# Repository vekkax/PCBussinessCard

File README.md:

# PCB Business Card

The **PCB Business Card** is a hardware project inspired by the [Hackaday 2024 Business Card Contest](https://hackaday.io/contest/195949-2024-business-card-contest)   and the business cards created by [Salvaged Circuitry](https://www.youtube.com/watch?v=rEdWV4Augfc).

It is a compact and creative way to showcase your capabilities as a hardware designer while sharing your contact details. Beyond being a novelty, the card also functions as a (slightly impractical, but fun) development platform.

---

## Board Design

The PCB was designed using **KiCad**, along with plugins such as **KiKit** and the **Fabrication Toolkit** to generate production-ready files.

The board features:

- **[STM32L452CEU](Datasheets/stm32l452ce.pdf)** microcontroller  
- **[NT2H1311F0DTLH](Datasheets/NTAG213F_216F.pdf)** NFC tag  
- Integrated **PCB USB connector**  
- Optional **pin headers**, allowing the card to be used as a development board  

The USB connector supplies power to the microcontroller through a **[3.3 V LDO regulator](Datasheets/LM3480.pdf)** and includes ESD protection on the data lines using a **TVS diode**. A power LED is placed next to the connector for visual feedback.

The NFC tag is connected to a custom PCB antenna designed using NXP’s [NFC Antenna Design Tool](https://community.nxp.com/t5/NFC/bd-p/nfc).  
This tool provides a convenient interface to design PCB NFC antennas (especially for NXP tags/readers) based on user-defined constraints. ST also provides a similar [antenna design tool](https://eds.st.com/antenna/#/).

---

### Bill of Materials (BOM)

| Reference | Value | Footprint | Quantity |
|---------|------|-----------|----------|
| C1–C4, C7–C9 | 100 nF | 0402 | 7 |
| C5 | 10 nF | 0402 | 1 |
| C6 | 1 µF | 0402 | 1 |
| D1 | RCLAMP0582B | SOT-416 | 1 |
| D2 | LED | 0603 | 1 |
| IC1 | NT2H1311F0DTL | SOT1312AB2 | 1 |
| R1 | 120 Ω | 0603 | 1 |
| SW1 | SMD push button | 4.6×1.8×1.9 mm | 1 |
| U1 | STM32L452CEU | QFN-48 | 1 |
| U2 | LM3480-3.3 | SOT-23 | 1 |

> **Note**  
> Reference designators were removed from the PCB layout to improve the visual appearance of the board.

---

## Fabrication

For fabrication, **KiCad’s KiKit** and **JLCPCB’s Fabrication Toolkit** plugins were used.

### Panelization

KiKit was used to panelize the PCB. Each panel contains **four PCB business cards**, separated by mouse bites and surrounded by left and right rails.

The panel configuration file can be found here:  
`PCBussinesCard_Circuit/Panels/panel_config.json`

For more information on KiKit panelization, refer to the official documentation:  
https://yaqwsx.github.io/KiKit/latest/panelization/examples/

### Manufacturing

Manufacturing was done using **JLCPCB**, with production files generated via the JLCPCB Fabrication Toolkit plugin.

---

## Software

The USB connector is used to expose the board as a **USB Mass Storage Device**, allowing a host computer to read and write files (for example, a digital CV) directly to the microcontroller’s internal flash memory.

This implementation uses the STM32’s built-in **USB Full-Speed device** support and the **Mass Storage Class (MSC)**.

The implementation was based on and adapted from the following guide:  
[STM32 USB MSC using Flash Memory – Embetronicx](https://embetronicx.com/tutorials/microcontrollers/stm32/stm32-usb-device-msc-using-flash-memory/)

---

### Flash Memory Configuration

According to the [RM0394 Reference Manual](Datasheets/rm0394-stm32l41xxx42xxx43xxx44xxx45xxx46xxx-advanced-armbased-32bit-mcus-stmicroelectronics.pdf), the STM32L452 has **512 KB of flash memory** organized in a single bank.

In this project:
- **64 KB** of flash is reserved for USB mass storage
- Starting at **Page 127**
- Flash start address:  
  **`0x0803F800`**

---

## STM32CubeIDE Configuration

1. Create a new STM32CubeIDE project for the **STM32L452**.
2. Under **Connectivity**, enable **USB Device (FS)**.
3. In **Middleware and Software Packs → USB_DEVICE**:
   - Set the class to **Mass Storage Class**
   - Set `MSC_MEDIA_PACKET` to **32 KB (32768 bytes)**

4. Ensure the USB clock is configured at **48 MHz** in the clock configuration tab.

5. Generate the project code.

---

## USB Mass Storage Implementation

Open the file: ```usb_device/App/usbd_storage_if.c```

### Storage Parameters

```c
#define STORAGE_LUN_NBR    1
#define STORAGE_BLK_NBR    128      // 128 blocks × 512 bytes = 64 KB
#define STORAGE_BLK_SIZ    0x200    // 512 bytes
```
---
### Flash Write Function
A helper function is added to write data to flash memory:

```c
#include <stdbool.h>

#define USB_FLASH_START_ADDRESS   (  0x0803F800 )    //USB Flash Address (page 127 in STM32L452)
#define TOTAL_USB_DEVICE_SIZE   ( STORAGE_BLK_NBR * STORAGE_BLK_SIZ )

/**
  * @brief  Writes data into the FLASH.
  * @param  buf: data buffer.
  * @param  blk_addr: Logical block address.
  * @param  blk_len: Blocks number.
  * @retval HAL_StatusTypeDef
  */
static HAL_StatusTypeDef write_data_to_flash( uint8_t *buf, uint32_t blk_addr, uint16_t blk_len )
{
  HAL_StatusTypeDef ret = HAL_OK;
  uint8_t           data[ TOTAL_USB_DEVICE_SIZE ];

  do
  {
    /* First copy the data to the local buffer from Flash */
    memcpy( data, (const void *)USB_FLASH_START_ADDRESS, TOTAL_USB_DEVICE_SIZE );
    
    /* Make modifications in the local buffer */
    memcpy((void*)&data[blk_addr*STORAGE_BLK_SIZ], buf, (blk_len*STORAGE_BLK_SIZ));
    
    ret = HAL_FLASH_Unlock();
    if( ret != HAL_OK )
    {
      break;
    }
    
    /* Erase the Flash */
    FLASH_EraseInitTypeDef EraseInitStruct;
    uint32_t SectorError;
    EraseInitStruct.TypeErase     = FLASH_TYPEERASE_SECTORS;
    EraseInitStruct.Sector        = FLASH_SECTOR_6;
    EraseInitStruct.NbSectors     = 1;                    //erase 1 sector(6)
    EraseInitStruct.VoltageRange  = FLASH_VOLTAGE_RANGE_3;
    
    ret = HAL_FLASHEx_Erase( &EraseInitStruct, &SectorError );
    
    /* Write the data to the Flash */
    for( uint32_t i = 0; i < TOTAL_USB_DEVICE_SIZE; i++)
    {
      ret = HAL_FLASH_Program( FLASH_TYPEPROGRAM_BYTE,
                  ( USB_FLASH_START_ADDRESS + i ),
                  data[i]
                  );
    
      if( ret != HAL_OK )
      {
        break;
      }
    }
    
    HAL_FLASH_Lock();
  } while( false );

  return( ret );
}
```
The function:

1. Copies existing flash contents to a RAM buffer

2. Modifies the buffer with new data

3. Erases the corresponding flash sector

4. Writes the updated data back to flash

---
### Write Callback
```c
int8_t STORAGE_Write_FS(uint8_t lun, uint8_t *buf, uint32_t blk_addr, uint16_t blk_len)
{
  UNUSED(lun);
  return write_data_to_flash(buf, blk_addr, blk_len);
}

```
---
### Read Callback
Reading data is simpler and can be done directly from flash:

```c
int8_t STORAGE_Read_FS(uint8_t lun, uint8_t *buf, uint32_t blk_addr, uint16_t blk_len)
{
  UNUSED(lun);
  memcpy(
    buf,
    (const void *)(USB_FLASH_START_ADDRESS + (blk_addr * STORAGE_BLK_SIZ)),
    blk_len * STORAGE_BLK_SIZ
  );
  return USBD_OK;
}

```
---
### Usage
1. Flash the firmware to the board.

2. Connect the PCB Business Card via USB.

3. A removable USB drive will appear.

4. Format the drive if prompted.

5. Files can now be read from and written to the device.

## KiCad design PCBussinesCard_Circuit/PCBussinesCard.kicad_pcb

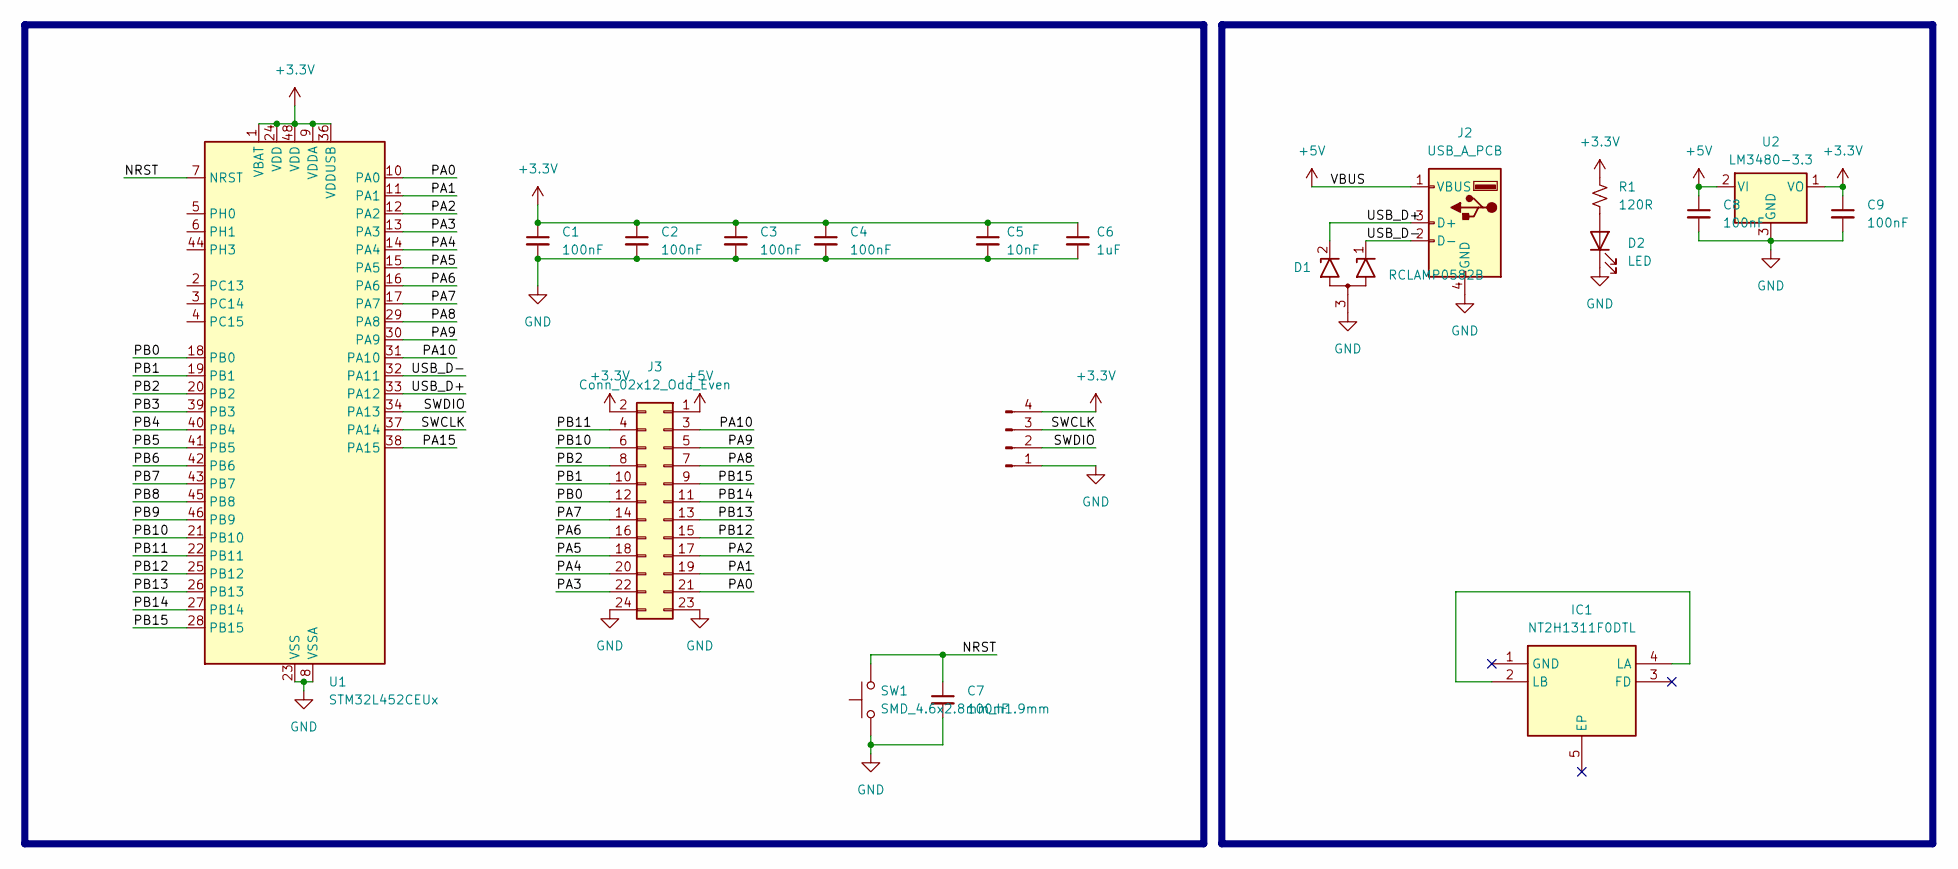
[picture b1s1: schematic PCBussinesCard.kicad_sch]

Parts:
C1, C2, C3, C4, C7, C8, C9: 100nF; C_0402_1005Metric
C5: 10nF; C_0402_1005Metric
C6: 1uF; C_0402_1005Metric
D1: RCLAMP0582B; SOT-416
D2: LED; LED_0603_1608Metric
IC1: NT2H1311F0DTL; SON50P200X150X50-5N; Manufacturer_Part_Number NT2H1311F0DTL
J1: Conn_01x04_Pin; PinHeader_1x04_P2.54mm_Horizontal
J2: USB_A_PCB; PCB_USB_A
J3: Conn_02x12_Odd_Even; PinSocket_2x12_P2.54mm_Vertical
R1: 120R; R_0603_1608Metric
SW1: SMD_4.6x2.8mm_h1.9mm; Push_SMD_4.6x2.8mm_h1.9mm
U1: STM32L452CEUx; QFN-48-1EP_7x7mm_P0.5mm_EP5.6x5.6mm
U2: LM3480-3.3; SOT-23

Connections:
+3.3V: C1.1, C2.1, C3.1, C4.1, C5.1, C6.1, C9.1, J1.4, J3.2, R1.1, U1.1 (VBAT), U1.9 (VDDA), U1.24 (VDD), U1.36 (VDDUSB), U1.48 (VDD), U2.1 (VO)
+5V: C8.1, J2.1 (VBUS), J3.1, U2.2 (VI)
/NRST: C7.1, SW1.2, U1.7 (NRST)
/PA0: J3.21, U1.10 (PA0)
/PA1: J3.19, U1.11 (PA1)
/PA2: J3.17, U1.12 (PA2)
/PA3: J3.22, U1.13 (PA3)
/PA4: J3.20, U1.14 (PA4)
/PA5: J3.18, U1.15 (PA5)
/PA6: J3.16, U1.16 (PA6)
/PA7: J3.14, U1.17 (PA7)
/PA8: J3.7, U1.29 (PA8)
/PA9: J3.5, U1.30 (PA9)
/PA10: J3.3, U1.31 (PA10)
/PA15: U1.38 (PA15)
/PB0: J3.12, U1.18 (PB0)
/PB1: J3.10, U1.19 (PB1)
/PB2: J3.8, U1.20 (PB2)
/PB3: U1.39 (PB3)
/PB4: U1.40 (PB4)
/PB5: U1.41 (PB5)
/PB6: U1.42 (PB6)
/PB7: U1.43 (PB7)
/PB8: U1.45 (PB8)
/PB9: U1.46 (PB9)
/PB10: J3.6, U1.21 (PB10)
/PB11: J3.4, U1.22 (PB11)
/PB12: J3.15, U1.25 (PB12)
/PB13: J3.13, U1.26 (PB13)
/PB14: J3.11, U1.27 (PB14)
/PB15: J3.9, U1.28 (PB15)
/SWCLK: J1.3, U1.37 (PA14)
/SWDIO: J1.2, U1.34 (PA13)
/USB_D+: D1.2 (K2), J2.3 (D+), U1.33 (PA12)
/USB_D-: D1.1 (K1), J2.2 (D-), U1.32 (PA11)
GND: C1.2, C2.2, C3.2, C4.2, C5.2, C6.2, C7.2, C8.2, C9.2, D1.3 (A), D2.1 (K), J1.1, J2.4 (GND), J3.23, J3.24, SW1.1, U1.8 (VSSA), U1.23 (VSS), U1.35 (VSS), U1.47 (VSS), U1.49 (VSS), U2.3 (GND)
unnamed: D2.2 (A), R1.2
unnamed: IC1.2 (LB), IC1.4 (LA)

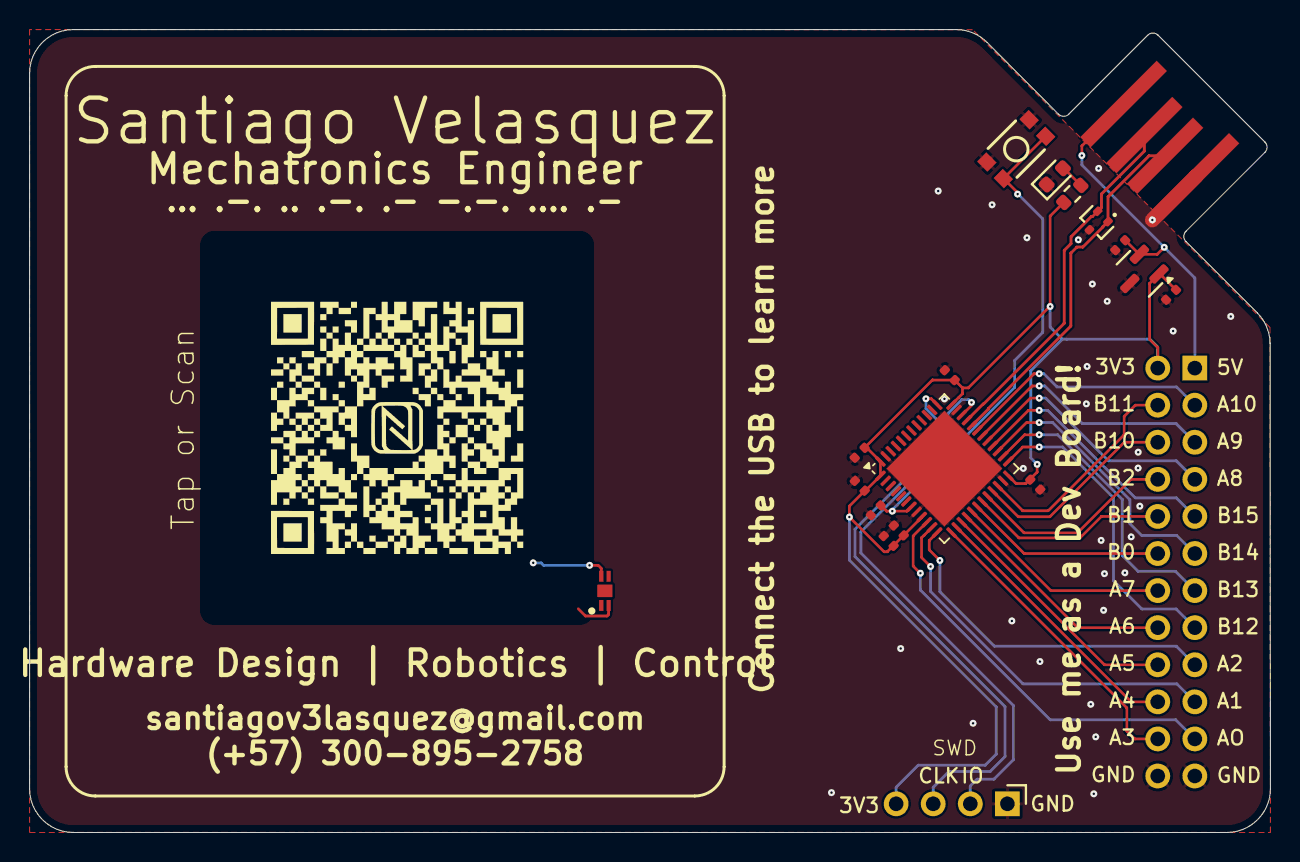
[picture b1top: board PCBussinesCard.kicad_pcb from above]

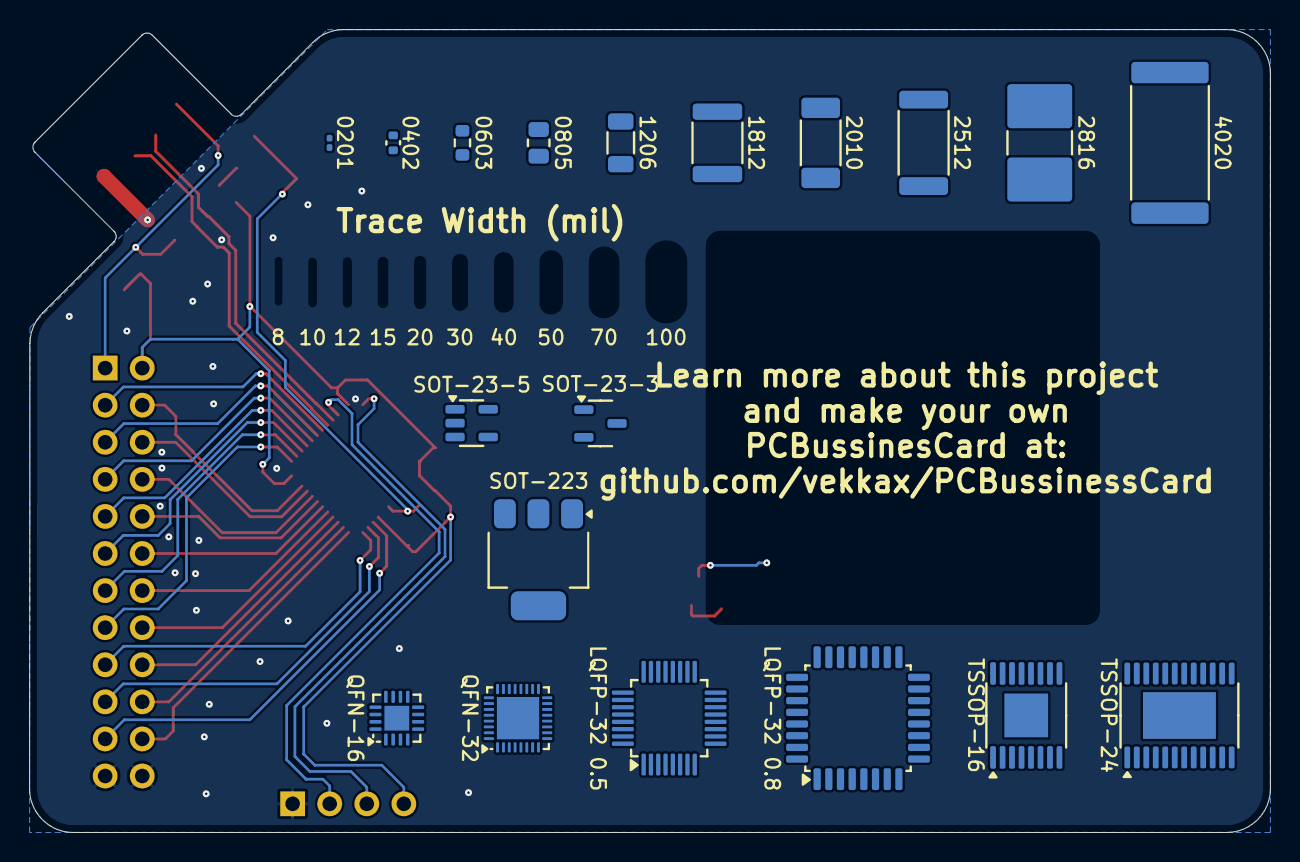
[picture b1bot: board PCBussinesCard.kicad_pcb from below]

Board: 2 copper layers, 85.0 x 55.0 mm, 38 parts (19 on the bottom side), 30 nets.

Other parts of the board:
0201: C_0201_0603Metric
0402: R_0402_1005Metric
0603: R_0603_1608Metric
0805: R_0805_2012Metric
1206: R_1206_3216Metric
1812: R_1812_4532Metric
2010: R_2010_5025Metric_Pad1.40x2.65mm_HandSolder
2512: R_2512_6332Metric
2816: R_2816_7142Metric
4020: R_4020_10251Metric
LQFP-32 0.5: LQFP-32_5x5mm_P0.5mm
LQFP-32 0.8: LQFP-32_7x7mm_P0.8mm
QFN-16: QFN-16-1EP_3x3mm_P0.5mm_EP1.7x1.7mm
QFN-32 : QFN-32-1EP_4x4mm_P0.4mm_EP2.9x2.9mm
SOT-23-3: SOT-23-3
SOT-23-5: SOT-23-5
SOT-223: SOT-223
TSSOP-16: TSSOP-16-1EP_4.4x5mm_P0.65mm_EP3x3mm
TSSOP-24: TSSOP-24-1EP_4.4x7.8mm_P0.65mm_EP3.2x5mm

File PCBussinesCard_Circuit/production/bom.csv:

Designator,Footprint,Quantity,Value,LCSC Part #
0201,0201,1,C_0201_0603Metric,
0402,0402,1,R_0402_1005Metric,
0603,0603,1,R_0603_1608Metric,
0805,0805,1,R_0805_2012Metric,
1206,1206,1,R_1206_3216Metric,
1812,1812,1,R_1812_4532Metric,
2010,2010,1,R_2010_5025Metric_Pad1.40x2.65mm_HandSolder,
2512,2512,1,R_2512_6332Metric,
2816,2816,1,R_2816_7142Metric,
4020,4020,1,R_4020_10251Metric,
"C1, C2, C3, C4, C7",0402,5,100nF,
C5,0402,1,10nF,
C6,0402,1,1uF,
D1,SOT-416,1,RCLAMP0582B,
D2,0603,1,LED,
IC1,SON50P200X150X50-5N,1,NT2H1311F0DTL,
J1,PinHeader_1x04_P2.54mm_Horizontal,1,Conn_01x04_Pin,
J2,PCB_USB_A,1,USB_A_PCB,
J3,PinSocket_2x12_P2.54mm_Vertical,1,Conn_02x12_Odd_Even,
LQFP-32 0.5,LQFP-32_5x5mm_P0.5mm,1,LQFP-32_5x5mm_P0.5mm,
LQFP-32 0.8,LQFP-32_7x7mm_P0.8mm,1,LQFP-32_7x7mm_P0.8mm,
QFN-16,QFN-16-1EP_3x3mm_P0.5mm_EP1.7x1.7mm,1,QFN-16-1EP_3x3mm_P0.5mm_EP1.7x1.7mm,
QFN-32 ,QFN-32-1EP_4x4mm_P0.4mm_EP2.9x2.9mm,1,QFN-32-1EP_4x4mm_P0.4mm_EP2.9x2.9mm,
R1,0603,1,120R,
SOT-223,SOT-223,1,SOT-223,
SOT-23-3,SOT-23-3,1,SOT-23-3,
SOT-23-5,SOT-23-5,1,SOT-23-5,
SW1,Push_SMD_4.6x2.8mm_h1.9mm,1,SMD_4.6x2.8mm_h1.9mm,
TSSOP-16,TSSOP-16-1EP_4.4x5mm_P0.65mm_EP3x3mm,1,TSSOP-16-1EP_4.4x5mm_P0.65mm_EP3x3mm,
TSSOP-24,TSSOP-24-1EP_4.4x7.8mm_P0.65mm_EP3.2x5mm,1,TSSOP-24-1EP_4.4x7.8mm_P0.65mm_EP3.2x5mm,
U1,LQFP-48_7x7mm_P0.5mm,1,STM32L552CCTx,
U2,DFN-6-1EP_2x2mm_P0.65mm_EP1.01x1.7mm,1,AP7370-33FDC,

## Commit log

2025-12-07 Schematic and layout sketch
2025-12-10 added QR code image
2025-12-11 provisional antena added
2025-12-11 fixed nfc antena
2025-12-11 Added new Qrcode
2025-12-11 nfc qr code
2025-12-11 cleanup and reorganizing
2026-01-23 Version 1.0
2026-01-29 Production V1.0
2026-01-29 Production Panels V1.0
2026-02-01 README added and unnecesary files removed
